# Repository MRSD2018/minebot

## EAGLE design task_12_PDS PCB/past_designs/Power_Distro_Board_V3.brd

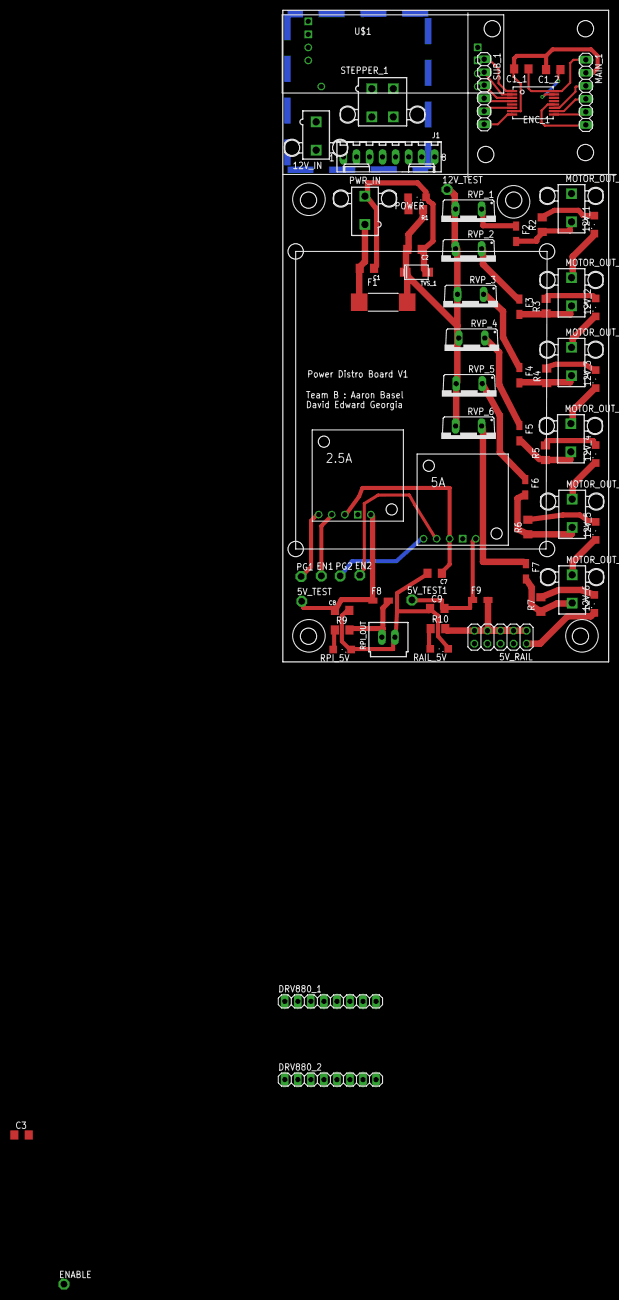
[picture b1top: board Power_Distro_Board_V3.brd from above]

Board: 2 copper layers, 63.5 x 127.0 mm, 70 parts (0 on the bottom side), 61 nets.

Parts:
2.5A, 5A: POLOLU_5VREG; SIP5
5V_RAIL: 5V 5A; 2X05
5V_TEST, 5V_TEST1, 12V_TEST: TPPAD1-13; P1-13
12V_1, 12V_2, 12V_3, 12V_4, 12V_5, 12V_6: GREEN; SML1206
12V_IN: 5566-2
C1: 150uF; C1206
C1_1: 100nF; C1206
C1_2, C7, C8, C9: 10uF; C1206
C2: 100uF; C1206
C3: C1206
DRV880_1, DRV880_2: 1X08
EN1, EN2: TPPAD1-13; P1-13
ENABLE: TPPAD1-13; P1-13
ENC_1: ENCODER_AS5045B; SSOP16
F1: 60VDC 50A; NANO
F2, F3, F4, F5, F6, F7: 60VDC 20A; R1206W
F8: 60VDC 3A; R1206W
F9: 60VDC 5A; R1206W
J1: 22-27-2081-08; 6410-08
MAIN_1: 1X06
MOTOR_OUT_1, MOTOR_OUT_2, MOTOR_OUT_3, MOTOR_OUT_4, MOTOR_OUT_5, MOTOR_OUT_6: 5566-2
PG1, PG2: TPPAD1-13; P1-13
POWER: GREEN; SML1206
PWR_IN: 5566-2
R1: 500; R1206
R2, R3, R4, R5, R6, R7: 470; R1206
R9, R10: 150; R1206
RAIL_5V: GREEN; SML1206
RPI_5V: GREEN; SML1206
RPI_OUT: C-GRID-02-70543; 70543-02
RVP_1, RVP_2, RVP_3, RVP_4, RVP_5, RVP_6: 15V; TO220ACS
STEPPER_1: 5566-4
SUB_1: 1X06
TVS_1: 16V; DO-214AC
U$1: POLOLU_24VSTEPUP; 2X4PIN_REG

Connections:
5V_REG: 2.5A.VOUT, 5V_TEST.TP, C8.2, F8.1
5V_REG1: F8.2, R9.2, RPI_OUT.1
5V_REG3: 5V_RAIL.1, 5V_RAIL.3, 5V_RAIL.5, 5V_RAIL.7, 5V_RAIL.9, F9.2, R10.2
12V_REG: 12V_TEST.TP, C2.2, F1.VIN-, R1.1, RVP_1.A, RVP_2.A, RVP_3.A, RVP_4.A, RVP_5.A, RVP_6.A, TVS_1.1
12V_REG_TVS: 2.5A.VIN, 5A.VIN, C7.2
24V_1: DRV880_2.1, U$1.VOUT1, U$1.VOUT2
A1: DRV880_2.6, STEPPER_1.4
A2: DRV880_2.5, STEPPER_1.3
A_1: ENC_1.3, SUB_1.3
B1: DRV880_2.3, STEPPER_1.1
B2: DRV880_2.4, STEPPER_1.2
B_1: ENC_1.4, SUB_1.4
CLK_1: ENC_1.10, MAIN_1.4
CSN_1: ENC_1.11, MAIN_1.3
DIR: DRV880_1.8, J1.2
DO_1: ENC_1.9, MAIN_1.5
EN: DRV880_1.1, J1.7
FAULT: DRV880_2.7, J1.8
GND: 2.5A.GND, 5A.GND, 5V_RAIL.2, 5V_RAIL.4, 5V_RAIL.6, 5V_RAIL.8, 5V_RAIL.10, 12V_1.C, 12V_2.C, 12V_3.C, 12V_4.C, 12V_5.C, 12V_6.C, C1.1, C2.1, C3.1, C7.1, C8.1, C9.1, DRV880_2.2, DRV880_2.8, J1.1, MOTOR_OUT_1.2, MOTOR_OUT_2.2, MOTOR_OUT_3.2, MOTOR_OUT_4.2, MOTOR_OUT_5.2, MOTOR_OUT_6.2, POWER.C, PWR_IN.2, RAIL_5V.C, RPI_5V.C, RPI_OUT.2, TVS_1.2, U$1.GND3, U$1.GND4
GND_1: C1_1.2, C1_2.2, ENC_1.7, MAIN_1.2
I_1: ENC_1.6, SUB_1.5
M0: DRV880_1.3, J1.5
M1: DRV880_1.2, J1.6
MAG_DEC_N_1: ENC_1.2, SUB_1.2
MAG_INC_N_1: ENC_1.1, SUB_1.1
unnamed: POWER.A, R1.2
unnamed: 2.5A.PG, PG1.TP
unnamed: C1.2, F1.VIN+, PWR_IN.1
unnamed: C1_2.1, ENC_1.15
unnamed: F2.1, RVP_1.C
unnamed: 2.5A.EN, EN1.TP
unnamed: F6.1, RVP_5.C
unnamed: 5A.PG, PG2.TP
unnamed: 12V_1.A, R2.2
unnamed: R9.1, RPI_5V.A
unnamed: R10.1, RAIL_5V.A
unnamed: F2.2, MOTOR_OUT_1.1, R2.1
unnamed: 12V_5.A, R6.2
unnamed: F3.1, RVP_2.C
unnamed: 5A.EN, EN2.TP
unnamed: 12V_2.A, R3.2
unnamed: F6.2, MOTOR_OUT_5.1, R6.1
unnamed: F3.2, MOTOR_OUT_2.1, R3.1
unnamed: F7.1, RVP_6.C
unnamed: 12V_6.A, R7.2
unnamed: F4.1, RVP_3.C
unnamed: F7.2, MOTOR_OUT_6.1, R7.1
unnamed: 12V_3.A, R4.2
unnamed: F4.2, MOTOR_OUT_3.1, R4.1
unnamed: F5.1, RVP_4.C
unnamed: 12V_4.A, R5.2
unnamed: F5.2, MOTOR_OUT_4.1, R5.1
unnamed: 12V_IN.2, U$1.GND1, U$1.GND2
unnamed: 12V_IN.1, U$1.VIN1, U$1.VIN2
unnamed: ENABLE.TP, U$1.ENABLE
unnamed: 5A.VOUT, 5V_TEST1.TP, C9.2, F9.1
PDIO_1: ENC_1.8, SUB_1.6
PWM_1: ENC_1.12, MAIN_1.6
SLEEP: DRV880_1.6, J1.4
STEP: DRV880_1.7, J1.3
VIN_1: C1_1.1, ENC_1.16, MAIN_1.1

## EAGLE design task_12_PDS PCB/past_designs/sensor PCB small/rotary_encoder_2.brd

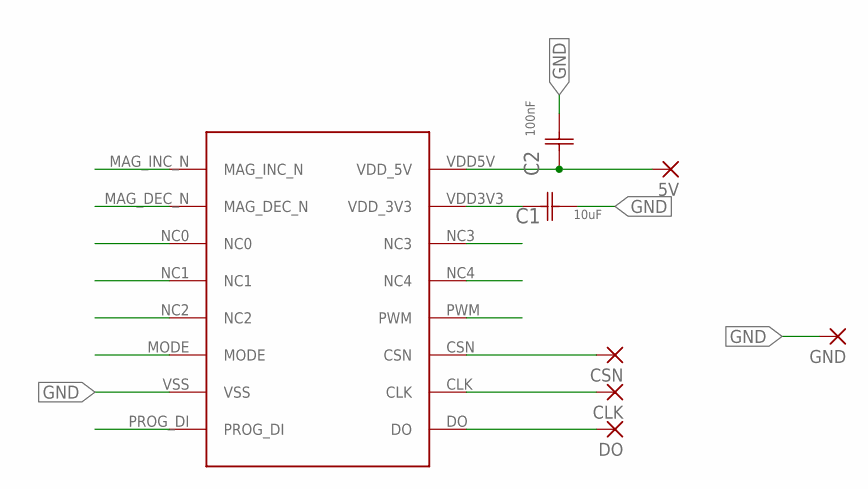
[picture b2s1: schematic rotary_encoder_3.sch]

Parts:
5V: 1,6/0,8
C1: 10uF; CAP_0805_100NF
C2: 100nF; CAP_0805_100NF
CLK: 1,6/0,8
CSN: 1,6/0,8
DO: 1,6/0,8
GND: 1,6/0,8
U$1: AS5045_ROTARY_ENCODER

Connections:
5V: 5V.1, C2.1 (C1), U$1.VDD5V (VDD_5V)
CLK: CLK.1, U$1.CLK
CSN: CSN.1, U$1.CSN
DO: DO.1, U$1.DO
GND: C1.2 (C2), C2.2 (C2), GND.1, U$1.VSS
unnamed: C1.1 (C1), U$1.VDD3V3 (VDD_3V3)

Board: 2 copper layers, 8 parts (0 on the bottom side), 6 nets, no tracks yet.

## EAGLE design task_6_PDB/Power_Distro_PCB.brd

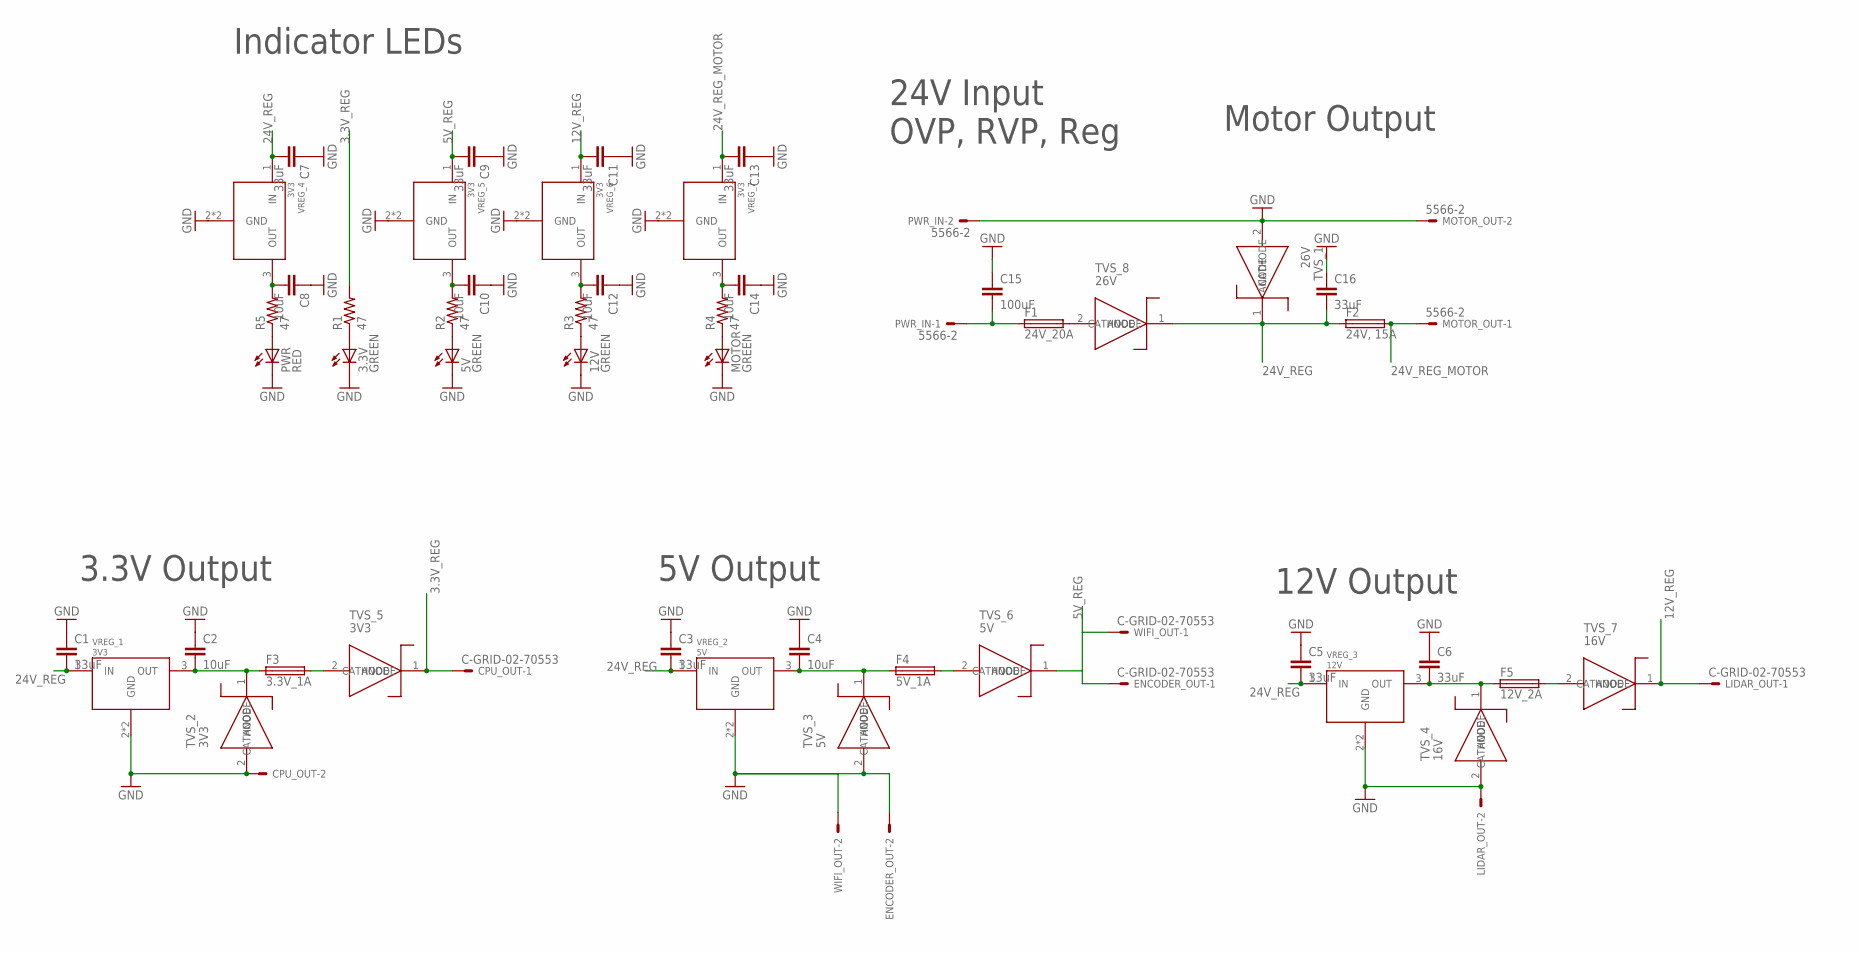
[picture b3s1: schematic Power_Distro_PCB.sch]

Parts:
3.3V, 5V, 12V: GREEN; SML1206
C1, C3, C5, C6, C7, C9, C11, C13, C16: 33uF; C1206
C2, C4, C8, C10, C12, C14: 10uF; C1206
C15: 100uF; C1206
CPU_OUT: C-GRID-02-70553; 70553-02
ENCODER_OUT: C-GRID-02-70553; 70553-02
F1: 24V_20A; TE5
F2: 24V, 15A; TE5
F3: 3.3V_1A; TE5
F4: 5V_1A; TE5
F5: 12V_2A; TE5
LIDAR_OUT: C-GRID-02-70553; 70553-02
MOTOR: GREEN; SML1206
MOTOR_OUT: 5566-2
PWR: RED; SML1206
PWR_IN: 5566-2
R1, R2, R3, R4, R5: 47; R1206
TVS_1, TVS_8: 26V; DO-214AC
TVS_2, TVS_5: 3V3; DO-214AA
TVS_3, TVS_6: 5V; DO-214AC
TVS_4, TVS_7: 16V; DO-214AC
VREG_1, VREG_4, VREG_5, VREG_6, VREG_7: 3V3; TO-263-3
VREG_2: 5V; TO-263-3
VREG_3: 12V; TO-263-3
WIFI_OUT: C-GRID-02-70553; 70553-02

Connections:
3.3V_REG: CPU_OUT.1, R1.2, TVS_5.1 (CATHODE)
5V_REG: C9.2, ENCODER_OUT.1, TVS_6.1 (CATHODE), VREG_5.1 (IN), WIFI_OUT.1
12V_REG: C11.2, LIDAR_OUT.1, TVS_7.1 (CATHODE), VREG_6.1 (IN)
24V_REG: C1.2, C3.2, C5.2, C7.2, C16.2, F2.1, TVS_1.1 (CATHODE), TVS_8.1 (CATHODE), VREG_1.1 (IN), VREG_2.1 (IN), VREG_3.1 (IN), VREG_4.1 (IN)
24V_REG_MOTOR: C13.2, F2.2, MOTOR_OUT.1, VREG_7.1 (IN)
GND: 3.3V.C, 5V.C, 12V.C, C1.1, C2.1, C3.1, C4.1, C5.1, C6.1, C7.1, C8.1, C9.1, C10.1, C11.1, C12.1, C13.1, C14.1, C15.1, C16.1, CPU_OUT.2, ENCODER_OUT.2, LIDAR_OUT.2, MOTOR.C, MOTOR_OUT.2, PWR.C, PWR_IN.2, TVS_1.2 (ANODE), TVS_2.2 (ANODE), TVS_3.2 (ANODE), TVS_4.2 (ANODE), VREG_1.2 (GND), VREG_1.4 (GND), VREG_2.2 (GND), VREG_2.4 (GND), VREG_3.2 (GND), VREG_3.4 (GND), VREG_4.2 (GND), VREG_4.4 (GND), VREG_5.2 (GND), VREG_5.4 (GND), VREG_6.2 (GND), VREG_6.4 (GND), VREG_7.2 (GND), VREG_7.4 (GND), WIFI_OUT.2
unnamed: F1.2, TVS_8.2 (ANODE)
unnamed: 3.3V.A, R1.1
unnamed: C15.2, F1.1, PWR_IN.1
unnamed: F3.2, TVS_5.2 (ANODE)
unnamed: 5V.A, R2.1
unnamed: C2.2, F3.1, TVS_2.1 (CATHODE), VREG_1.3 (OUT)
unnamed: C4.2, F4.1, TVS_3.1 (CATHODE), VREG_2.3 (OUT)
unnamed: 12V.A, R3.1
unnamed: MOTOR.A, R4.1
unnamed: C6.2, F5.1, TVS_4.1 (CATHODE), VREG_3.3 (OUT)
unnamed: F4.2, TVS_6.2 (ANODE)
unnamed: PWR.A, R5.1
unnamed: C8.2, R5.2, VREG_4.3 (OUT)
unnamed: C10.2, R2.2, VREG_5.3 (OUT)
unnamed: C12.2, R3.2, VREG_6.3 (OUT)
unnamed: C14.2, R4.2, VREG_7.3 (OUT)
unnamed: F5.2, TVS_7.2 (ANODE)

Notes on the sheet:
Indicator LEDs
24V Input OVP, RVP, Reg
Motor Output
3.3V Output
5V Output
12V Output

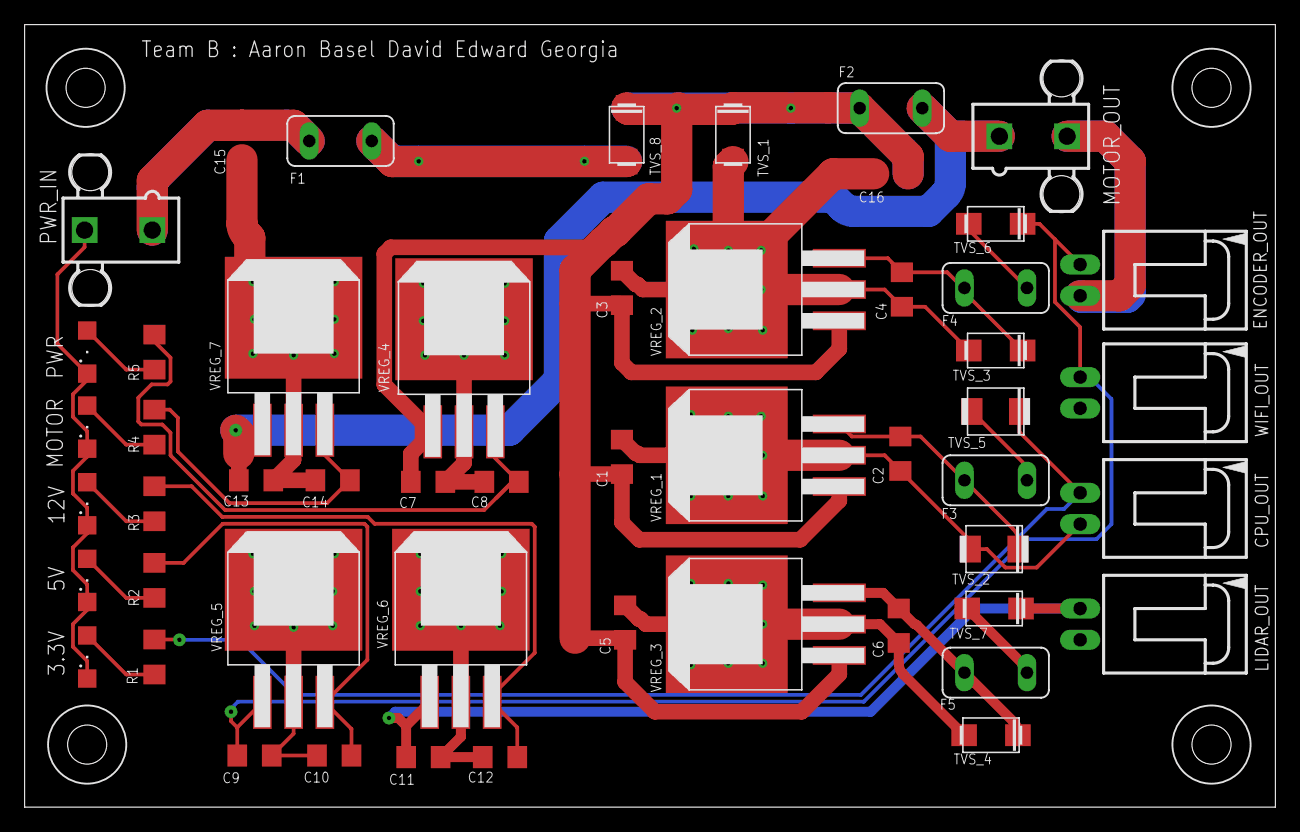
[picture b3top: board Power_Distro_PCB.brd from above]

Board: 2 copper layers, 101.6 x 63.6 mm, 52 parts (0 on the bottom side), 23 nets.
